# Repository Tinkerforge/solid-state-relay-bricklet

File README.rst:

Solid State Relay Bricklet
==========================

This repository contains the firmware source code and the hardware design
files. The documentation generator configs can be found at
https://github.com/Tinkerforge/generators

Repository Content
------------------

software/:
 * examples/: Examples for all supported languages
 * build/: Compiled files
 * src/: Source code of firmware
 * Makefile: Makefile to build project

hardware/:
 * Contains KiCad project files and additionally schematics as PDF

datasheets/:
 * Contains datasheets for sensors and complex ICs that are used

Hardware
--------

The hardware is designed with the open source EDA Suite KiCad
(http://www.kicad.org). Before you are able to open the files,
you have to install the Tinkerforge kicad-libraries
(https://github.com/Tinkerforge/kicad-libraries). You can either clone
them directly in hardware/ or clone them in a separate folder and
symlink them into hardware/
(ln -s kicad_path/kicad-libraries project_path/hardware). After that you
can open the .pro file in hardware/ with KiCad and from there view and
modify the schematics and the PCB layout.

Software
--------

If you want to do your own Brick/Bricklet firmware development we highly
recommend that you use our build environment setup script and read the
tutorial (https://www.tinkerforge.com/en/doc/Tutorials/Tutorial_Build_Environment/Tutorial.html).

To compile the C code we recommend you to install the newest GNU Arm Embedded
Toolchain (https://launchpad.net/gcc-arm-embedded/+download).
You also need to install bricklib (https://github.com/Tinkerforge/bricklib)
and brickletlib (https://github.com/Tinkerforge/brickletlib).

You can either clone it directly in software/src/ or clone it in a
separate folder and symlink it into software/src/
(ln -s bricklib_path/bricklib project_path/software/src/ and
ln -s brickletlib_path/brickletlib project_path/software/src/).
Finally make sure to have CMake installed
(http://www.cmake.org/cmake/resources/software.html).

After that you can build the firmware by invoking make in software/.
The firmware (.bin) can then be found in software/build/ and uploaded
with brickv (click button "Flashing" on start screen).

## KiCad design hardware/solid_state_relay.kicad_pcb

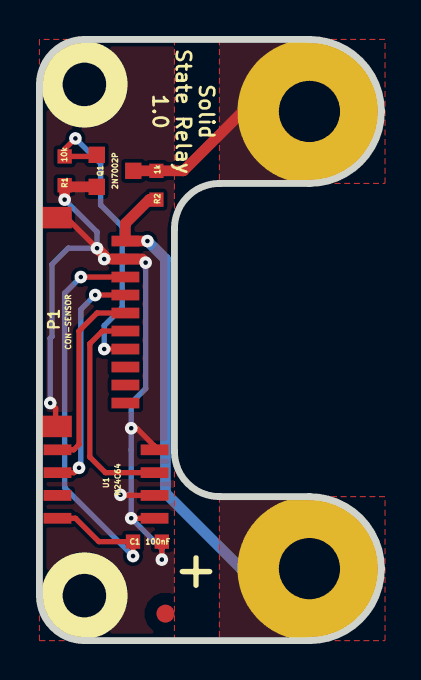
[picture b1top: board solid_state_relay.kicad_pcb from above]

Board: 2 copper layers, 19.0 x 33.4 mm, 13 parts (0 on the bottom side), 8 nets.

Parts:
C1: 100nF; 0603
Fiducial_Mark: VAL**; Fiducial_Mark
P1: CON-SENSOR
P2, P3: TST; Drill_32
Q1: 2N7002P; SOT23GDS
R1: 10k; 0603
R2: 1k; 0603
U1: M24C64; SOIC8
U2, U3: DRILL; DRILL_NP
VAL: CE_5mm
VAL#2: WEEE_7mm

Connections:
+5V: P1.1, P3.1, R2.1
GND: C1.2, P1.2, P1.EP, Q1.S, R1.2, U1.1, U1.2, U1.4
unnamed: P1.4, U1.6
unnamed: P1.5, U1.5
unnamed: P1.6, U1.3
unnamed: P1.7, Q1.G, R1.1
unnamed: P2.1, Q1.D, R2.2
VCC: C1.1, P1.3, U1.8

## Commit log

2014-05-27 Remove "dual"
2014-05-27 Add firmware for Solid State Relay
2014-05-27 Remove unnecessary includes
2014-05-27 Add examples for Solid State Relay Bricklet (LabVIEW still missing)
2014-07-15 java: Replace System.console() usage with an Eclipse compatible pattern
2014-07-31 Add missing toolchain info
2014-07-31 Fix identifier
2014-07-31 add hardware files for solid state relay
2014-07-31 add schematic
2014-07-31 Add Bricklet prefix (2) to device identifier
2014-08-05 datasheets for ssr accessories
2014-08-06 Add LabVIEW example
2014-08-06 Fix typos
2014-12-02 Use ReadLine instead of ReadKey for C# example
2015-02-13 vbnet: Use ReadLine instead of ReadKey
    Because ReadKey doesn't work with a pipe as stdin on the RED Brick.
2015-03-02 windows: Stop cmake from searching for mingw32-make.exe
    Using MinGW Makefiles as generator makes cmake search for mingw32-make.exe
    which might not be installed because GnuWin32's make.exe is used instead.
2015-07-25 Make JavaScript browser example textarea readonly
2015-07-27 Cleanup C/C++, C#, Java, Python and Ruby examples
2015-07-29 Reformat changelog
2015-08-07 Use full device class name in Python example
2015-08-12 Fix minor warnings in C/C++ example
2015-08-17 Cleanup Delphi example
2015-08-18 Unify example loop logic
2015-08-19 Cleanup Perl example
2015-09-09 Duplicate cmake call to fix bug during cmake creation
2015-09-25 drc check
2015-09-25 fix fiducial
2015-10-08 Generator based example cleanup
2015-11-12 matlab: Fix callback handling for R2014a
    http://undocumentedmatlab.com/blog/matlab-callbacks-for-java-events-in-r2014a
2015-11-25 Include date and commit into changelog
2016-05-18 c: Add missing device destroy call
2016-06-29 Whitespace
2016-07-01 Make the change UID comment more explicit
2017-06-02 octave: Use javaObject instead of deprecated java_new
2017-12-07 mathematica: Also generate .nb files
2018-01-26 c: Fine-tune define placement
2018-02-19 javascript: Close div tag correctly
2018-02-20 Cleanup KiCad libraries config
    Ensure LibDir=kicad-libraries and LibName1=tinkerforge.
    Remove special library.
2018-05-24 perl: Use strict in examples
2018-06-28 Fix readme
2018-07-11 Add Makefile with docker support
2018-07-11 Update directory structure and build instructions
2018-07-11 Remove obsolete generate_makefile scripts
2018-11-06 Add rust examples
2018-11-07 rust: Accept host names for ip connection, fix naming inconsistencies
2018-12-14 Add go examples.
2018-12-18 go: Change import path.
2018-12-18 go: Change import path again.
2018-12-20 rust: Reformat examples.
2019-01-24 mqtt: Add examples.
2019-01-24 mqtt: Fix example header.
2019-01-24 mqtt: Remove executable bit in example permissions.
2019-01-24 go: Minor example fixes.
2019-01-24 mqtt: Minor example fixes.
2019-01-29 rust: Fix unused loop index.
2019-05-07 Don't clear monoflop time on monoflop abort to match documentation
2020-01-13 examples: Use python3 input instead of python2 raw_input.
2020-01-13 examples: mqtt: Remove trailing whitespace.
2020-03-23 mqtt: Update for loop style
2020-04-07 examples: rust: Always block when calling bindings functions.
2021-10-25 Update KiCad link
    https://www.kicad.org/blog/2021/10/Avoid-links-to-former-kicad-domain/
2022-07-06 Add license files.

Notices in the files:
hardware/solid_state_relay.kicad_pcb:
Licensed under CERN OHL v.1.1
Copyright (©) 2014, B.Nordmeyer
Copyright Tinkerforge GmbH 2014.
This documentation describes Open Hardware and is licensed under the
CERN OHL v. 1.1.
